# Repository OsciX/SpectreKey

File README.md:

# SpectreKey
A covert USB HID device built from an ATtiny84. Coming soon

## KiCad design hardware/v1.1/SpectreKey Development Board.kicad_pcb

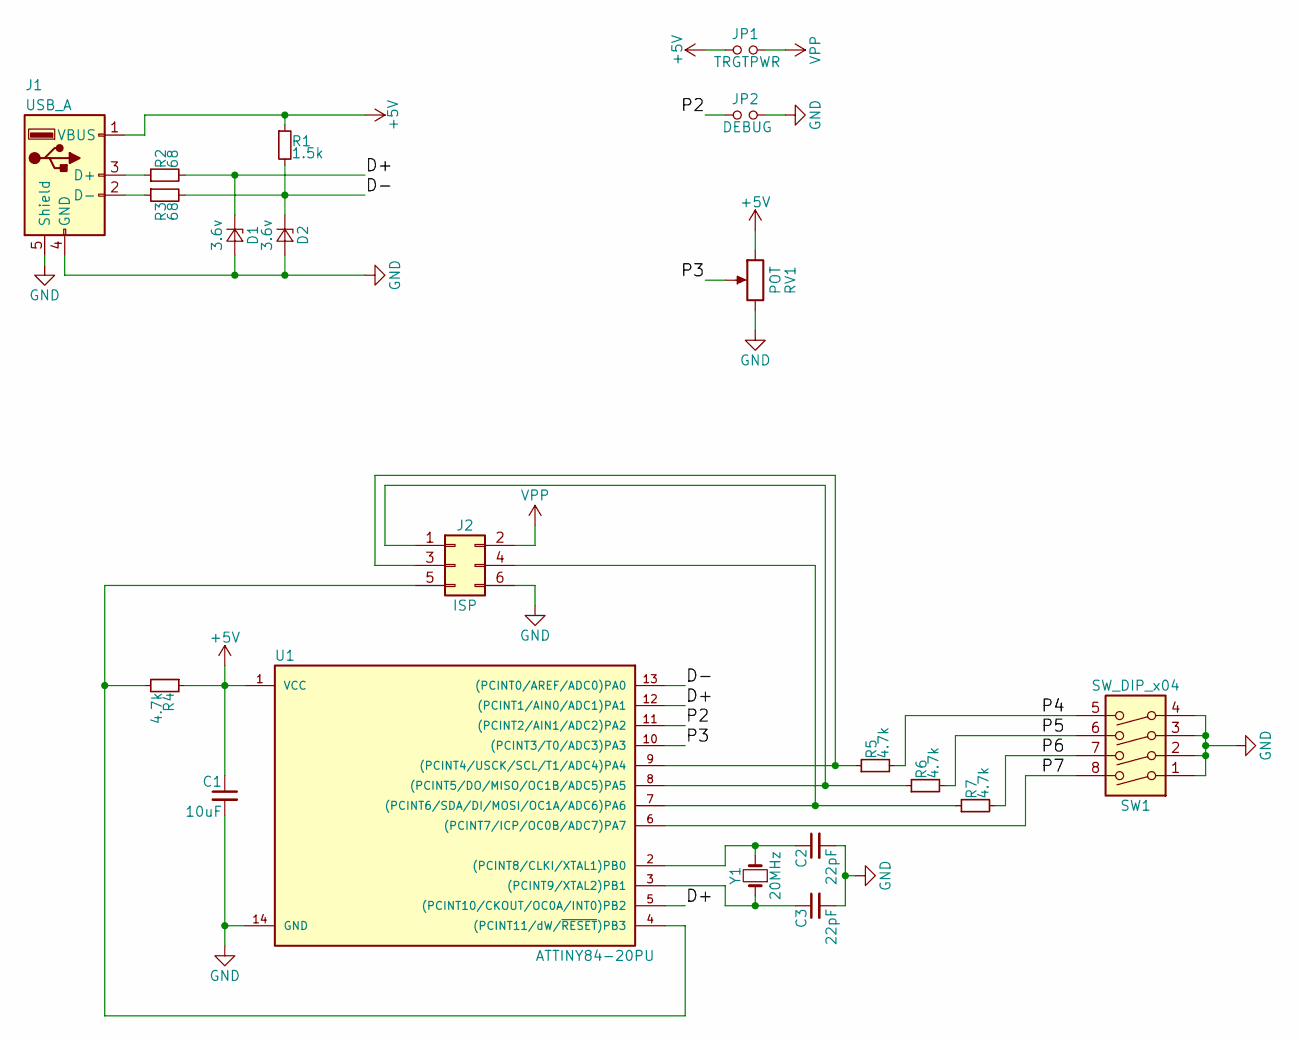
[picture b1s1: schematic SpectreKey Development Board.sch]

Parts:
C1: 10uF; C_Disc_D5.0mm_W2.5mm_P2.50mm
C2, C3: 22pF; C_Disc_D5.0mm_W2.5mm_P2.50mm
D1, D2: 3.6v; D_DO-35_SOD27_P7.62mm_Horizontal
J1: USB_A
J2: ISP; Pin_Header_Straight_2x03_Pitch2.54mm
JP1: TRGTPWR; Pin_Header_Straight_1x02_Pitch2.54mm
JP2: DEBUG; Pin_Header_Straight_1x02_Pitch2.54mm
R1: 1.5k; R_Axial_DIN0204_L3.6mm_D1.6mm_P5.08mm_Horizontal
R2, R3: 68; R_Axial_DIN0204_L3.6mm_D1.6mm_P5.08mm_Horizontal
R4, R5, R6, R7: 4.7k; R_Axial_DIN0204_L3.6mm_D1.6mm_P5.08mm_Horizontal
RV1: POT; Potentiometer_WirePads_Small
SW1: SW_DIP_x04; SW_DIP_x4_W7.62mm_Slide
U1: ATTINY84-20PU; DIP-14_W7.62mm
Y1: 20MHz; Crystal_HC49-U_Vertical

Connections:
+5V: C1.1, J1.1 (VBUS), JP1.1, R1.1, R4.1, RV1.1, U1.1 (VCC)
/D+: D1.1 (K), R2.2, U1.5 ((PCINT10/CKOUT/OC0A/INT0)PB2), U1.12 ((PCINT1/AIN0/ADC1)PA1)
/D-: D2.1 (K), R1.2, R3.2, U1.13 ((PCINT0/AREF/ADC0)PA0)
/P2: JP2.1, U1.11 ((PCINT2/AIN1/ADC2)PA2)
/P3: RV1.2, U1.10 ((PCINT3/T0/ADC3)PA3)
/P4: R5.2, SW1.5
/P5: R6.2, SW1.6
/P6: R7.2, SW1.7
/P7: SW1.8, U1.6 ((PCINT7/ICP/OC0B/ADC7)PA7)
GND: C1.2, C2.2, C3.2, D1.2 (A), D2.2 (A), J1.4 (GND), J1.5 (Shield), J2.6, JP2.2, RV1.3, SW1.1, SW1.2, SW1.3, SW1.4, U1.14 (GND)
unnamed: C2.1, U1.2 ((PCINT8/CLKI/XTAL1)PB0), Y1.2
unnamed: C3.1, U1.3 ((PCINT9/XTAL2)PB1), Y1.1
unnamed: J1.2 (D-), R3.1
unnamed: J1.3 (D+), R2.1
unnamed: J2.1, R6.1, U1.8 ((PCINT5/DO/MISO/OC1B/ADC5)PA5)
unnamed: J2.3, R5.1, U1.9 ((PCINT4/USCK/SCL/T1/ADC4)PA4)
unnamed: J2.4, R7.1, U1.7 ((PCINT6/SDA/DI/MOSI/OC1A/ADC6)PA6)
unnamed: J2.5, R4.2, U1.4 ((PCINT11/dW/~RESET~)PB3)
VPP: J2.2, JP1.2

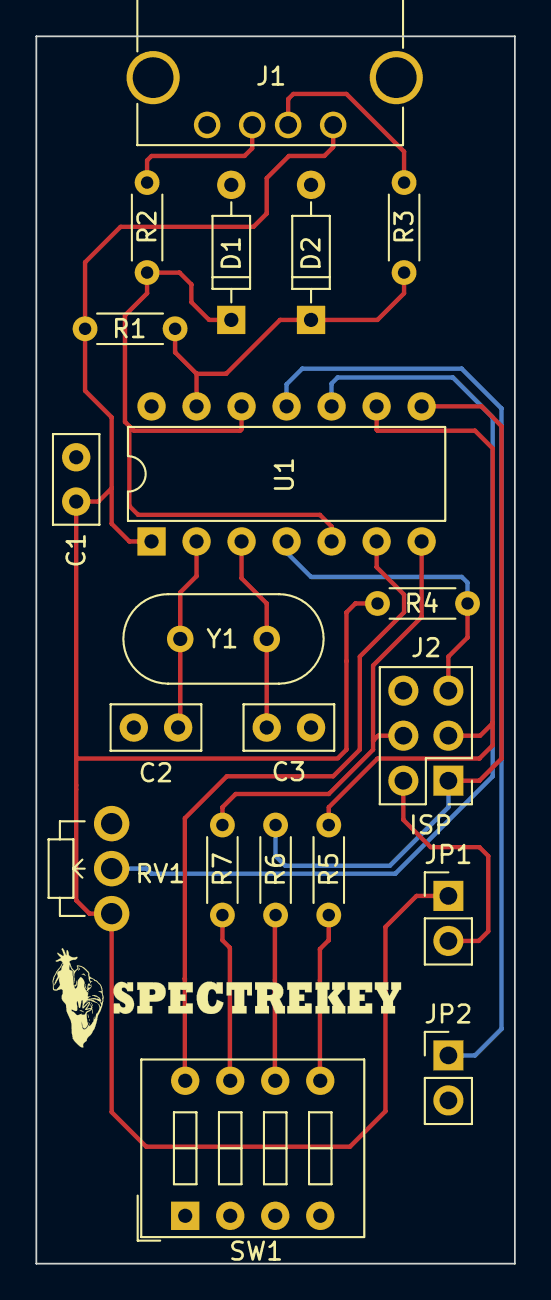
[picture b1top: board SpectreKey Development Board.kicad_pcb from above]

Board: 2 copper layers, 27.0 x 69.2 mm, 20 parts (0 on the bottom side), 19 nets.

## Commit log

2017-12-16 Add hardware revision 1.1
